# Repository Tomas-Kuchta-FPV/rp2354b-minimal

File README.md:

# RP2354B Minimal for KiCad 10

This is a realization of the Raspberry Pi RP2350 "Minimal" design.

My main objectives were to try the RP2354 for the internal flash and use the
"B" part for the extra GPIOs.

Going through
[Hardware design with RP2350](https://pip-assets.raspberrypi.com/categories/1214-rp2350/documents/RP-008280-DS-1-hardware-design-with-rp2350.pdf)
is required to do this stuff and expect good results. It has a link to the
original Kicad 7.0 version.

Changes from the original example:

* Kicad 10.0.3 (was Kicad 7.0). This just means opening the project with
  10.0.3 and immediately saving it.

* RP2354 (was RP2350). This means changing some of the components from
  do-not-populate to populate, and vice versa.

* Added JLCPCB part numbers. There are lots of options for most parts, and I
  just picked ones in stock.

Then I created the manufacturing output for JLCPCB, uploaded the files, and a
week later got apparently-working boards. "Apparently" in that the board I've
tried shows up as a usb drive (Windows) if I hold BOOTSEL, the debugger
(Raspberry Pi debugger under VS Code) connects and can load code, the board
tells me it's running at 150 MHz, and I can blink LEDs after soldering on
headers. I have not tried using the secondary flash, just the internal flash.
The boards look nicely done, including getting the inductors turned the right
way on all five boards I got.

One objective was to change as little as possible, partly because I have not
done any boards with JLCPCB using 0402 and such tiny traces, and would be
unlikely to be able debug it if something didn't work, i.e. the oscillator or
power supply. But they must be fine.

I told VS Code it's a pico-2 to connect to it, so some stuff is probably wrong
(like flash size).

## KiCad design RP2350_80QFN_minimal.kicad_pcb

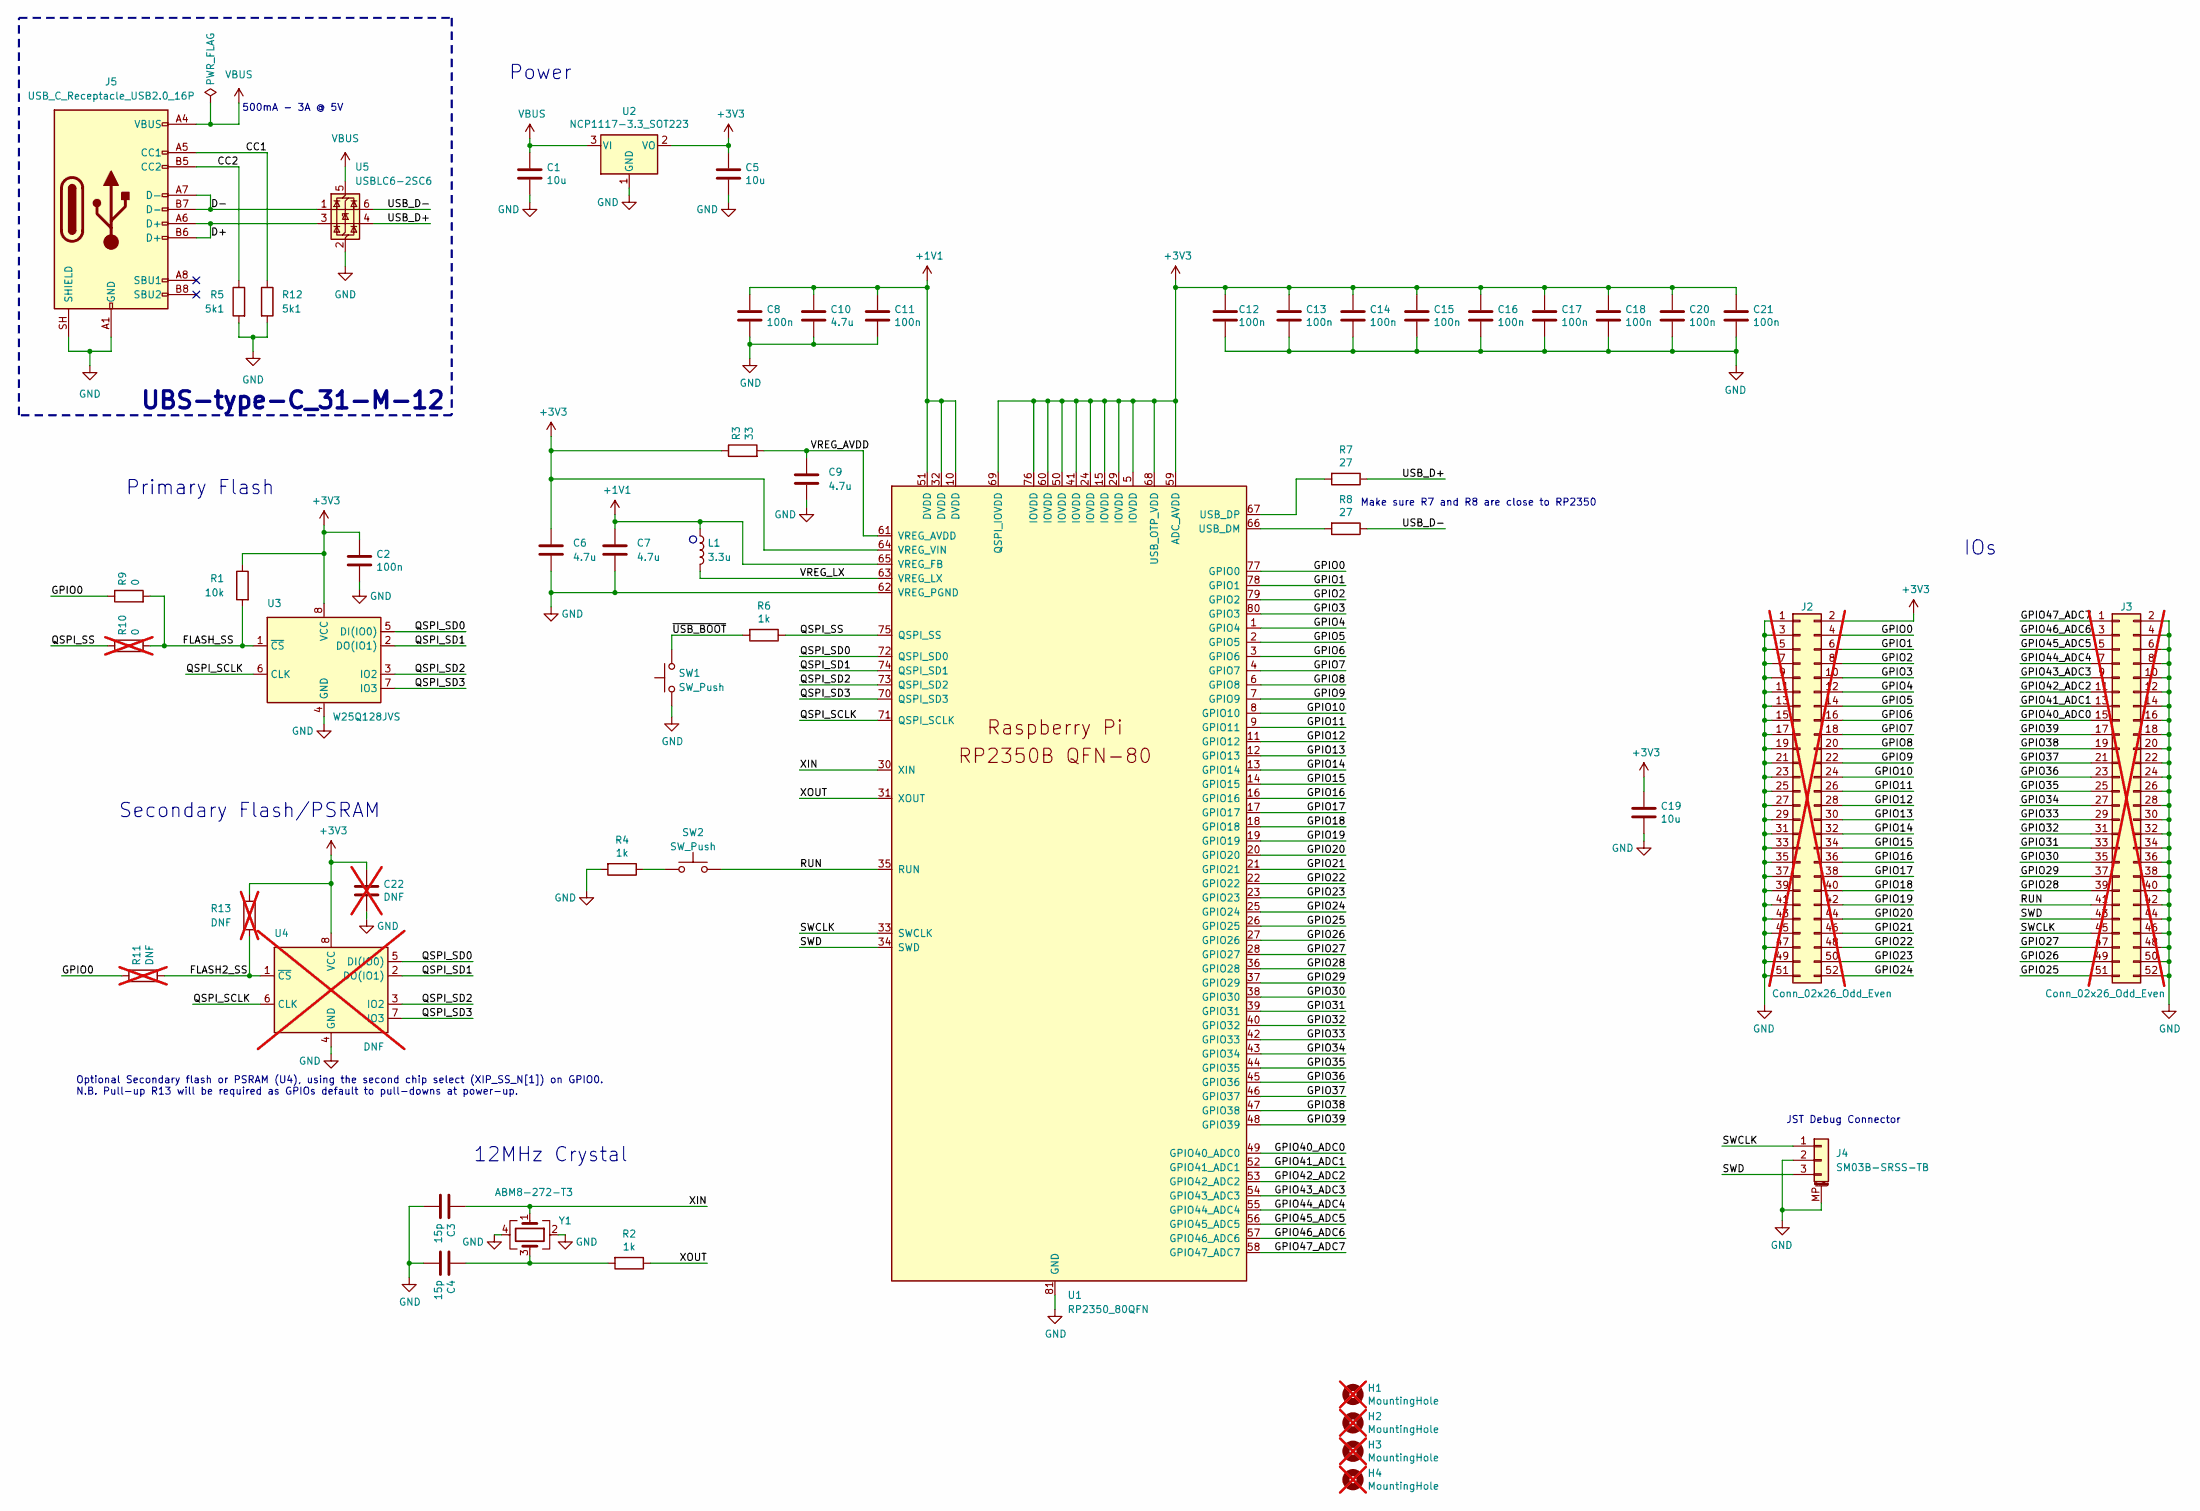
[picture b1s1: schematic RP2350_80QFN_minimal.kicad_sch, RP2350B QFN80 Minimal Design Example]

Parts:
C1, C5, C19: 10u; C_0805_2012Metric; LCSC PN C15850
C2, C8, C11, C12, C13, C14, C15, C16, C17, C18, C20, C21: 100n; C_0402_1005Metric; LCSC PN C16193311
C3, C4: 15p; C_0402_1005Metric; LCSC PN C307341
C6, C7: 4.7u; C_0402_1005Metric_small_pads; LCSC PN C368809
C9, C10: 4.7u; C_0402_1005Metric; LCSC PN C368809
C22: DNF; C_0402_1005Metric; not fitted
H1, H2, H3, H4: MountingHole; MountingHole_2.7mm_M2.5; not fitted
J2, J3: Conn_02x26_Odd_Even; PinHeader_2x26_P2.54mm_Vertical; not fitted
J4: SM03B-SRSS-TB; JST_SH_SM03B-SRSS-TB_1x03-1MP_P1.00mm_Horizontal; LCSC PN C160403
J5: USB_C_Receptacle_USB2.0_16P; USB_C_Receptacle_HRO_TYPE-C-31-M-12; LCSC C165948
L1: 3.3u; L_pol_2016; LCSC PN C42411119
R1: 10k; R_0402_1005Metric; LCSC PN C25744
R2, R4, R6: 1k; R_0402_1005Metric; LCSC PN C11702
R3: 33; R_0402_1005Metric; LCSC PN C25105
R5, R12: 5k1; R_0805_2012Metric_Pad1.20x1.40mm_HandSolder; LCSC C84375
R7, R8: 27; R_0402_1005Metric; LCSC PN C138021
R9: 0; R_0402_1005Metric; LCSC PN C17168
R10: 0; R_0402_1005Metric; not fitted
R11, R13: DNF; R_0402_1005Metric; not fitted
SW1, SW2: SW_Push; SW_Push_1P1T_NO_Vertical_Wuerth_434133025816; LCSC PN C115360
U1: RP2350_80QFN; RP2350-QFN-80-1EP_10x10_P0.4mm_EP3.4x3.4mm_ThermalVias; LCSC PN C39843328
U2: NCP1117-3.3_SOT223; SOT-223-3_TabPin2; LCSC PN C26537
U3: W25Q128JVS; SOIC-8_5.23x5.23mm_P1.27mm; LCSC PN C97521
U4: DNF; SOIC-8_5.23x5.23mm_P1.27mm; not fitted
U5: USBLC6-2SC6; SOT-23-6; LCSC C2827654
Y1: ABM8-272-T3; Crystal_SMD_3225-4Pin_3.2x2.5mm; LCSC PN C20625731

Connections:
+1V1: C7.1, C8.1, C10.1, C11.1, L1.1, U1.10 (DVDD), U1.32 (DVDD), U1.51 (DVDD), U1.65 (VREG_FB)
+3V3: C2.1, C5.1, C6.1, C12.1, C13.1, C14.1, C15.1, C16.1, C17.1, C18.1, C19.1, C20.1, C21.1, C22.1, J2.2, R1.1, R3.1, R13.1, U1.5 (IOVDD), U1.15 (IOVDD), U1.24 (IOVDD), U1.29 (IOVDD), U1.41 (IOVDD), U1.50 (IOVDD), U1.59 (ADC_AVDD), U1.60 (IOVDD), U1.64 (VREG_VIN), U1.68 (USB_OTP_VDD), U1.69 (QSPI_IOVDD), U1.76 (IOVDD), U2.2 (VO), U3.8 (VCC), U4.8 (VCC)
/CC1: J5.A5 (CC1), R12.1
/CC2: J5.B5 (CC2), R5.1
/D+: J5.A6 (D+), J5.B6 (D+), U5.3 (I/O2)
/D-: J5.A7 (D-), J5.B7 (D-), U5.1 (I/O1)
/FLASH2_SS: R11.2, R13.2, U4.1 (~CS)
/FLASH_SS: R1.2, R9.2, R10.2, U3.1 (~CS)
/GPIO0: J2.4, R9.1, R11.1, U1.77 (GPIO0)
/GPIO1: J2.6, U1.78 (GPIO1)
/GPIO2: J2.8, U1.79 (GPIO2)
/GPIO3: J2.10, U1.80 (GPIO3)
/GPIO4: J2.12, U1.1 (GPIO4)
/GPIO5: J2.14, U1.2 (GPIO5)
/GPIO6: J2.16, U1.3 (GPIO6)
/GPIO7: J2.18, U1.4 (GPIO7)
/GPIO8: J2.20, U1.6 (GPIO8)
/GPIO9: J2.22, U1.7 (GPIO9)
/GPIO10: J2.24, U1.8 (GPIO10)
/GPIO11: J2.26, U1.9 (GPIO11)
/GPIO12: J2.28, U1.11 (GPIO12)
/GPIO13: J2.30, U1.12 (GPIO13)
/GPIO14: J2.32, U1.13 (GPIO14)
/GPIO15: J2.34, U1.14 (GPIO15)
/GPIO16: J2.36, U1.16 (GPIO16)
/GPIO17: J2.38, U1.17 (GPIO17)
/GPIO18: J2.40, U1.18 (GPIO18)
/GPIO19: J2.42, U1.19 (GPIO19)
/GPIO20: J2.44, U1.20 (GPIO20)
/GPIO21: J2.46, U1.21 (GPIO21)
/GPIO22: J2.48, U1.22 (GPIO22)
/GPIO23: J2.50, U1.23 (GPIO23)
/GPIO24: J2.52, U1.25 (GPIO24)
/GPIO25: J3.51, U1.26 (GPIO25)
/GPIO26: J3.49, U1.27 (GPIO26)
/GPIO27: J3.47, U1.28 (GPIO27)
/GPIO28: J3.39, U1.36 (GPIO28)
/GPIO29: J3.37, U1.37 (GPIO29)
/GPIO30: J3.35, U1.38 (GPIO30)
/GPIO31: J3.33, U1.39 (GPIO31)
/GPIO32: J3.31, U1.40 (GPIO32)
/GPIO33: J3.29, U1.42 (GPIO33)
/GPIO34: J3.27, U1.43 (GPIO34)
/GPIO35: J3.25, U1.44 (GPIO35)
/GPIO36: J3.23, U1.45 (GPIO36)
/GPIO37: J3.21, U1.46 (GPIO37)
/GPIO38: J3.19, U1.47 (GPIO38)
/GPIO39: J3.17, U1.48 (GPIO39)
/GPIO40_ADC0: J3.15, U1.49 (GPIO40_ADC0)
/GPIO41_ADC1: J3.13, U1.52 (GPIO41_ADC1)
/GPIO42_ADC2: J3.11, U1.53 (GPIO42_ADC2)
/GPIO43_ADC3: J3.9, U1.54 (GPIO43_ADC3)
/GPIO44_ADC4: J3.7, U1.55 (GPIO44_ADC4)
/GPIO45_ADC5: J3.5, U1.56 (GPIO45_ADC5)
/GPIO46_ADC6: J3.3, U1.57 (GPIO46_ADC6)
/GPIO47_ADC7: J3.1, U1.58 (GPIO47_ADC7)
/QSPI_SCLK: U1.71 (QSPI_SCLK), U3.6 (CLK), U4.6 (CLK)
/QSPI_SD0: U1.72 (QSPI_SD0), U3.5 (DI(IO0)), U4.5 (DI(IO0))
/QSPI_SD1: U1.74 (QSPI_SD1), U3.2 (DO(IO1)), U4.2 (DO(IO1))
/QSPI_SD2: U1.73 (QSPI_SD2), U3.3 (IO2), U4.3 (IO2)
/QSPI_SD3: U1.70 (QSPI_SD3), U3.7 (IO3), U4.7 (IO3)
/QSPI_SS: R6.1, R10.1, U1.75 (QSPI_SS)
/RUN: J3.41, SW2.2, U1.35 (RUN)
/SWCLK: J3.45, J4.1, U1.33 (SWCLK)
/SWD: J3.43, J4.3, U1.34 (SWD)
/USB_D+: R7.1, U5.4 (I/O2)
/USB_D-: R8.1, U5.6 (I/O1)
/VREG_AVDD: C9.1, R3.2, U1.61 (VREG_AVDD)
/VREG_LX: L1.2, U1.63 (VREG_LX)
/XIN: C3.1, U1.30 (XIN), Y1.1
/XOUT: R2.1, U1.31 (XOUT)
/~USB_BOOT: R6.2, SW1.2
GND: C1.2, C2.2, C3.2, C4.2, C5.2, C6.2, C7.2, C8.2, C9.2, C10.2, C11.2, C12.2, C13.2, C14.2, C15.2, C16.2, C17.2, C18.2, C19.2, C20.2, C21.2, C22.2, J2.1, J2.3, J2.5, J2.7, J2.9, J2.11, J2.13, J2.15, J2.17, J2.19, J2.21, J2.23, J2.25, J2.27, J2.29, J2.31, J2.33, J2.35, J2.37, J2.39, J2.41, J2.43, J2.45, J2.47, J2.49, J2.51, J3.2, J3.4, J3.6, J3.8, J3.10, J3.12, J3.14, J3.16, J3.18, J3.20, J3.22, J3.24, J3.26, J3.28, J3.30, J3.32, J3.34, J3.36, J3.38, J3.40, J3.42, J3.44, J3.46, J3.48, J3.50, J3.52, J4.2, J4.MP (MountPin), J5.A1 (GND), J5.A12 (GND), J5.B1 (GND), J5.B12 (GND), J5.SH (SHIELD), R4.2, R5.2, R12.2, SW1.1, U1.62 (VREG_PGND), U1.81 (GND), U2.1 (GND), U3.4 (GND), U4.4 (GND), U5.2 (GND), Y1.2, Y1.4
unnamed: C4.1, R2.2, Y1.3
unnamed: R4.1, SW2.1
unnamed: R8.2, U1.66 (USB_DM)
unnamed: R7.2, U1.67 (USB_DP)
VBUS: C1.1, J5.A4 (VBUS), J5.A9 (VBUS), J5.B4 (VBUS), J5.B9 (VBUS), U2.3 (VI), U5.5 (VBUS)

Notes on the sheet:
Optional Secondary flash or PSRAM (U4), using the second chip select (XIP_SS_N[1]) on GPIO0. N.B. Pull-up R13 will be required as GPIOs default to pull-downs at power-up.
500mA - 3A @ 5V
IOs
12MHz Crystal
Primary Flash
JST Debug Connector
Make sure R7 and R8 are close to RP2350
Secondary Flash/PSRAM
Power
UBS-type-C_31-M-12

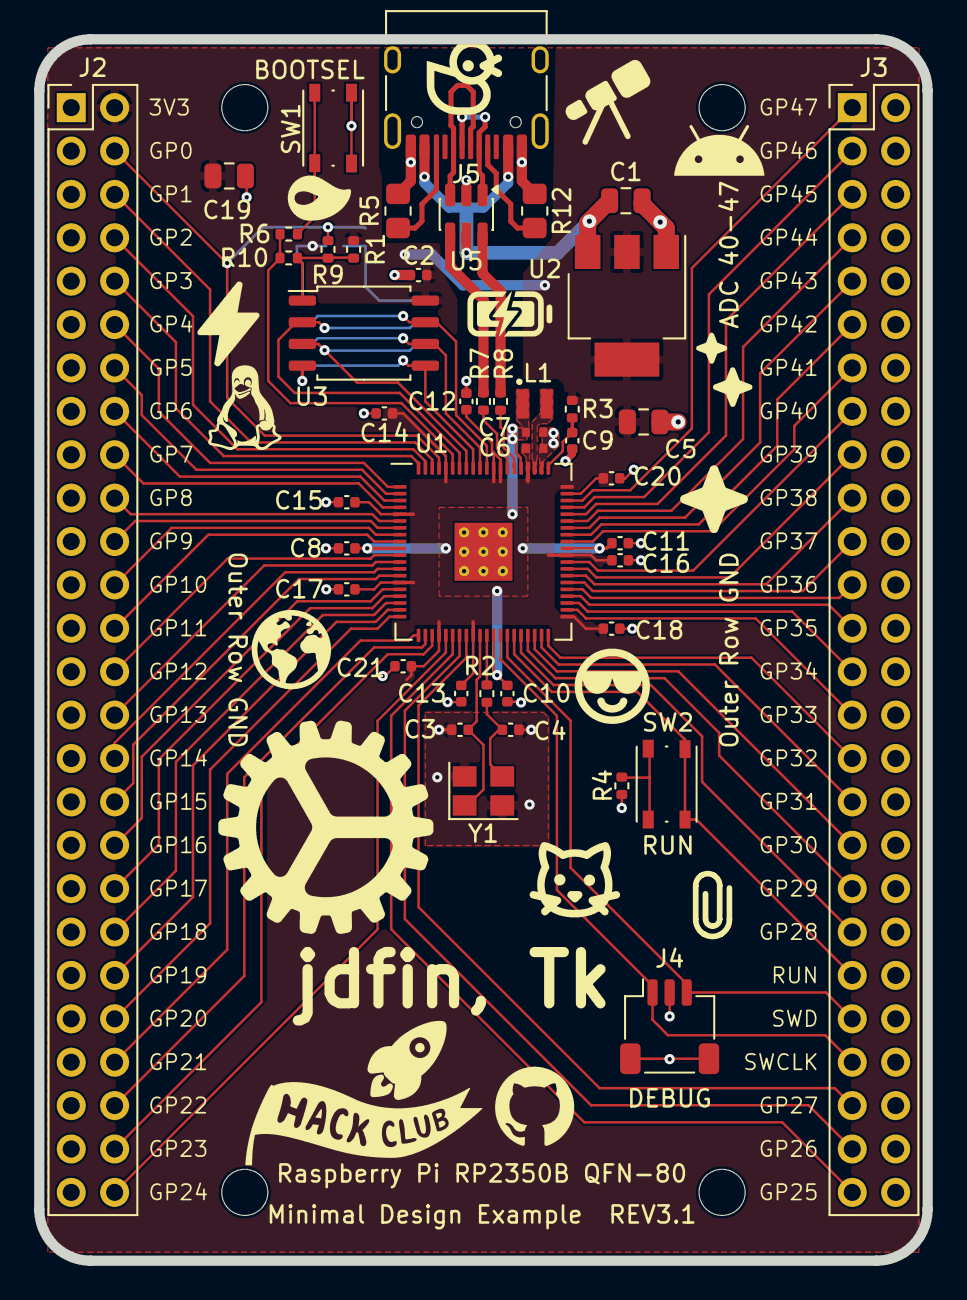
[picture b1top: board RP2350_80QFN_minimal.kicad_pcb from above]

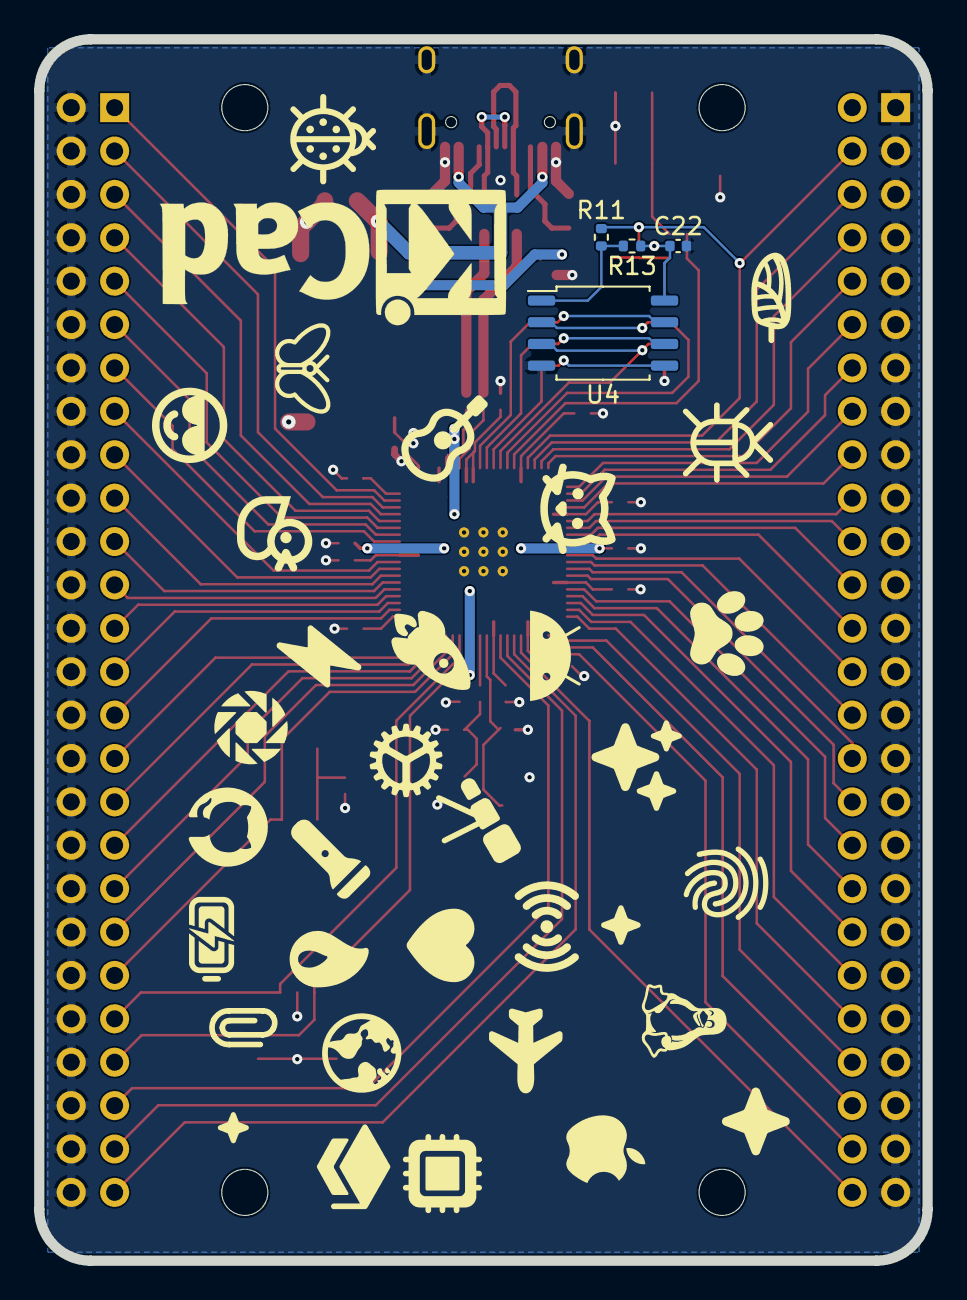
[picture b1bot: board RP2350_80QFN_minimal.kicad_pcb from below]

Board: 2 copper layers, 52.0 x 71.5 mm, 52 parts (4 on the bottom side), 78 nets.

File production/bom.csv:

Designator,Footprint,Quantity,Value,LCSC Part #
"C1, C19, C5",0805,3,10u,C15850
"C10, C6, C7, C9",0402,4,4.7u,C368809
"C11, C12, C13, C14, C15, C16, C17, C18, C2, C20, C21, C8",0402,12,100n,C16193311
"C3, C4",0402,2,15p,C307341
J4,JST_SH_SM03B-SRSS-TB_1x03-1MP_P1.00mm_Horizontal,1,SM03B-SRSS-TB,C160403
J5,USB_C_Receptacle_HRO_TYPE-C-31-M-12,1,USB_C_Receptacle_USB2.0_16P,C165948
L1,L_pol_2016,1,3.3u,C42411119
R1,0402,1,10k,C25744
"R12, R5",0805,2,5k1,C84375
"R2, R4, R6",0402,3,1k,C11702
R3,0402,1,33,C25105
"R7, R8",0402,2,27,C138021
R9,0402,1,0,C17168
"SW1, SW2",SW_Push_1P1T_NO_Vertical_Wuerth_434133025816,2,SW_Push,C115360
U1,RP2350-QFN-80-1EP_10x10_P0.4mm_EP3.4x3.4mm_ThermalVias,1,RP2350_80QFN,C39843328
U2,SOT-223-3_TabPin2,1,NCP1117-3.3_SOT223,C26537
U3,SOIC-8_5.23x5.23mm_P1.27mm,1,W25Q128JVS,C97521
U5,SOT-23-6,1,USBLC6-2SC6,C2827654
Y1,Crystal_SMD_3225-4Pin_3.2x2.5mm,1,ABM8-272-T3,C20625731

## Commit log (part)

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2026-06-08 original version
2026-06-08 saved with kicad 10.0.3
    Opened and saved the schematic an pcb files.
2026-06-08 added jlcpcb part numbers, configured do-not-pop
    Primary flash is configured as secondary.
    Through-hole connectors not populated.
2026-06-09 added .gitignore
2026-06-09 as submitted to jlcpcb for manufacturing
2026-06-17 added README
2026-06-17 added picture
